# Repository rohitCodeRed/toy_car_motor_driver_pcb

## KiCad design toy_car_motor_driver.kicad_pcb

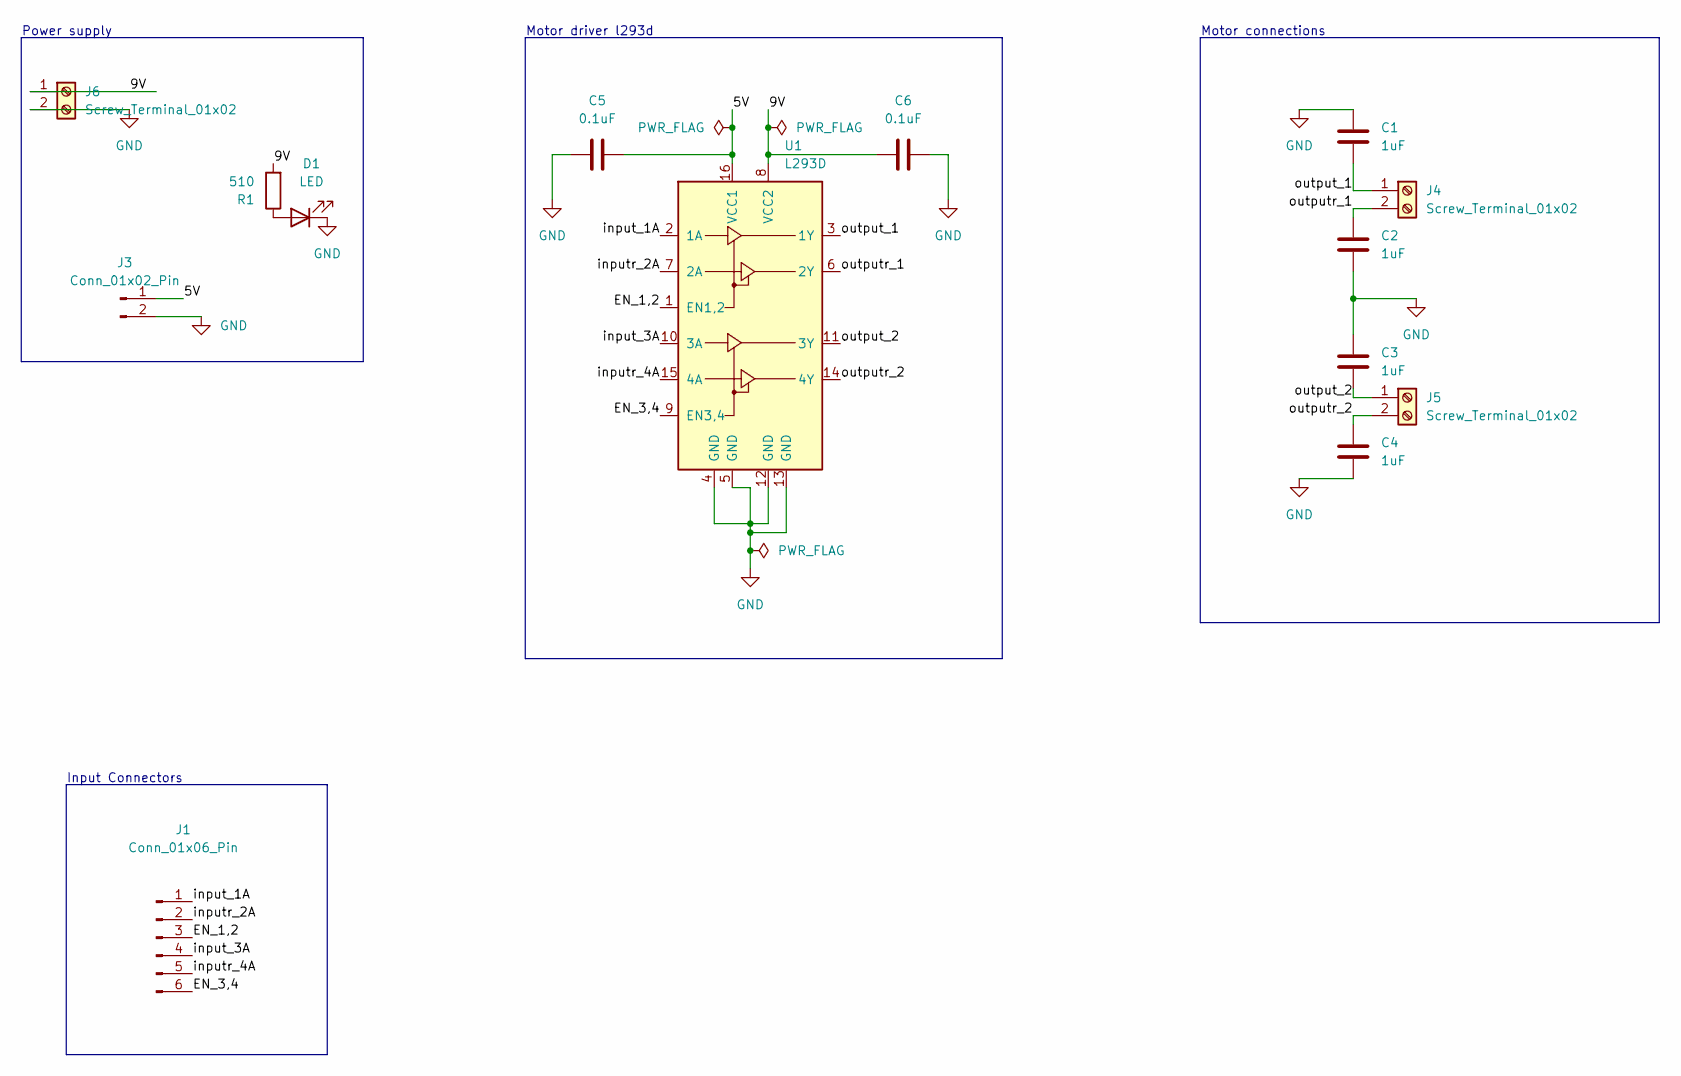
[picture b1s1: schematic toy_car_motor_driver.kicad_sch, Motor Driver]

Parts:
C1, C2, C3, C4: 1uF; C_Disc_D3.8mm_W2.6mm_P2.50mm
C5, C6: 0.1uF; C_Disc_D3.8mm_W2.6mm_P2.50mm
D1: LED; LED_D3.0mm
J1: Conn_01x06_Pin; PinHeader_1x06_P2.54mm_Vertical
J3: Conn_01x02_Pin; PinHeader_1x02_P2.54mm_Vertical
J4, J5, J6: Screw_Terminal_01x02; JWT_A3963_1x02_P3.96mm_Vertical
R1: 510; R_Axial_DIN0204_L3.6mm_D1.6mm_P7.62mm_Horizontal
U1: L293D; DIP-16_W7.62mm

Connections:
/5V: C5.2, J3.1, U1.16 (VCC1)
/9V: C6.1, J6.1, R1.2, U1.8 (VCC2)
/EN_1,2: J1.3, U1.1 (EN1,2)
/EN_3,4: J1.6, U1.9 (EN3,4)
/input_1A: J1.1, U1.2 (1A)
/input_3A: J1.4, U1.10 (3A)
/inputr_2A: J1.2, U1.7 (2A)
/inputr_4A: J1.5, U1.15 (4A)
/output_1: C1.2, J4.1, U1.3 (1Y)
/output_2: C3.2, J5.1, U1.11 (3Y)
/outputr_1: C2.1, J4.2, U1.6 (2Y)
/outputr_2: C4.1, J5.2, U1.14 (4Y)
GND: C1.1, C2.2, C3.1, C4.2, C5.1, C6.2, D1.1 (K), J3.2, J6.2, U1.4 (GND), U1.5 (GND), U1.12 (GND), U1.13 (GND)
unnamed: D1.2 (A), R1.1

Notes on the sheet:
Power supply
Input Connectors
Motor driver l293d
Motor connections

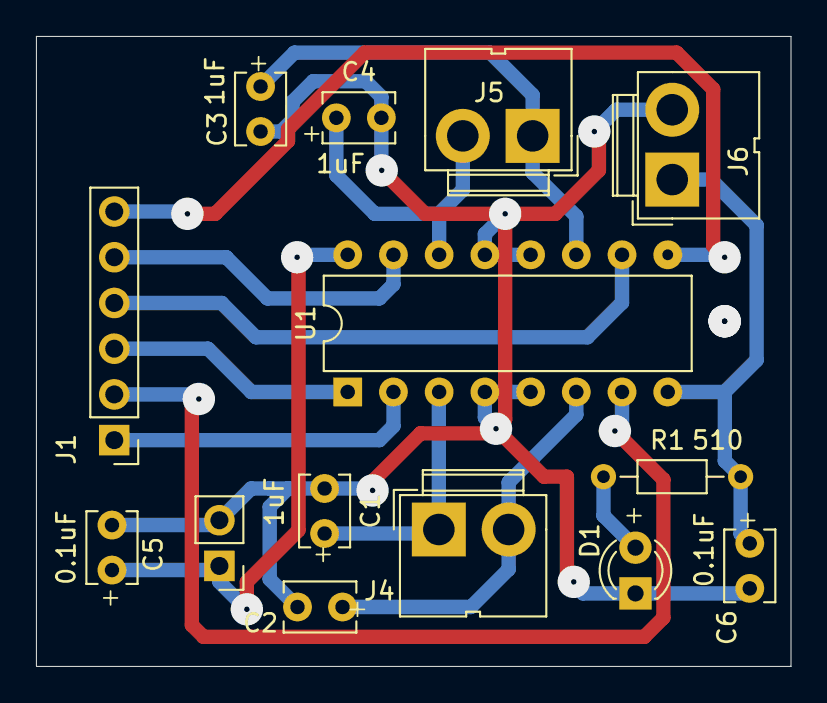
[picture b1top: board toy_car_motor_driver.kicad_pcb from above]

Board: 2 copper layers, 41.9 x 35.0 mm, 14 parts (0 on the bottom side), 14 nets.

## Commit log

2024-08-19 Added all components in motor drivers.
2024-08-19 added switches
2024-08-19 Added switches for input power
2024-08-24 Completed pcb design and routing
2024-09-23 made further changes
2024-10-18 Updated pcb
